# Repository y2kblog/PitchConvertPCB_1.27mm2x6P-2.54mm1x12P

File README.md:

# ピッチ変換基板(1.27mm 2×6P⇔2.54mm 1×12P)

## 概要

1.27mmピッチ2×6Pを2.54mmピッチ1×12Pに変換する基板です。

## 仕様
- ピンピッチ：1.27mm 2×6P ⇔ 2.54mm 1×12P
- 基板サイズ：10mm × 30.48mm
- 基板厚：1.6mm
- 基板色：緑
- 表面仕上げ：無鉛はんだ
- 両面スル―ホール
- 固定穴：25mmピッチ, M3×2穴

## 販売  
[スイッチサイエンス委託販売ページ](https://www.switch-science.com/catalog/6861/)（ボックスヘッダ付）  
※大量注文や在庫に関する問い合わせは[こちら](mailto:info.y2kb@gmail.com)までご連絡ください。

## 寸法

## License
MIT License, see `/LICENSE`.

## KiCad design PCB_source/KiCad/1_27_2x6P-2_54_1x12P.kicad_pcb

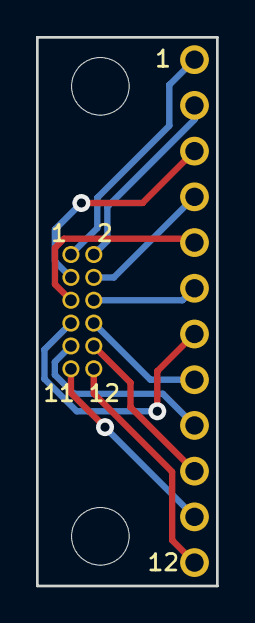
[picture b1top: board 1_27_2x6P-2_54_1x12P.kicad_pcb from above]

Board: 2 copper layers, 10.0 x 30.5 mm, 4 parts (0 on the bottom side), 12 nets.

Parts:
H1, H2: MountingHole; MountingHole_3.2mm_M3
J1: 1.27_2x6P; USER_DILhalf_6X2_NoSilk
J2: 2.54_1x12P; USER_SIL-12_NoSilk

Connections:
/1: J1.1, J2.1
/2: J1.2, J2.2
/3: J1.3, J2.3
/4: J1.4, J2.4
/5: J1.5, J2.5
/6: J1.6, J2.6
/7: J1.7, J2.7
/8: J1.8, J2.8
/9: J1.9, J2.9
/10: J1.10, J2.10
/11: J1.11, J2.11
/12: J1.12, J2.12

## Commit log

2020-09-09 add files
2020-12-26 add switch science page link
